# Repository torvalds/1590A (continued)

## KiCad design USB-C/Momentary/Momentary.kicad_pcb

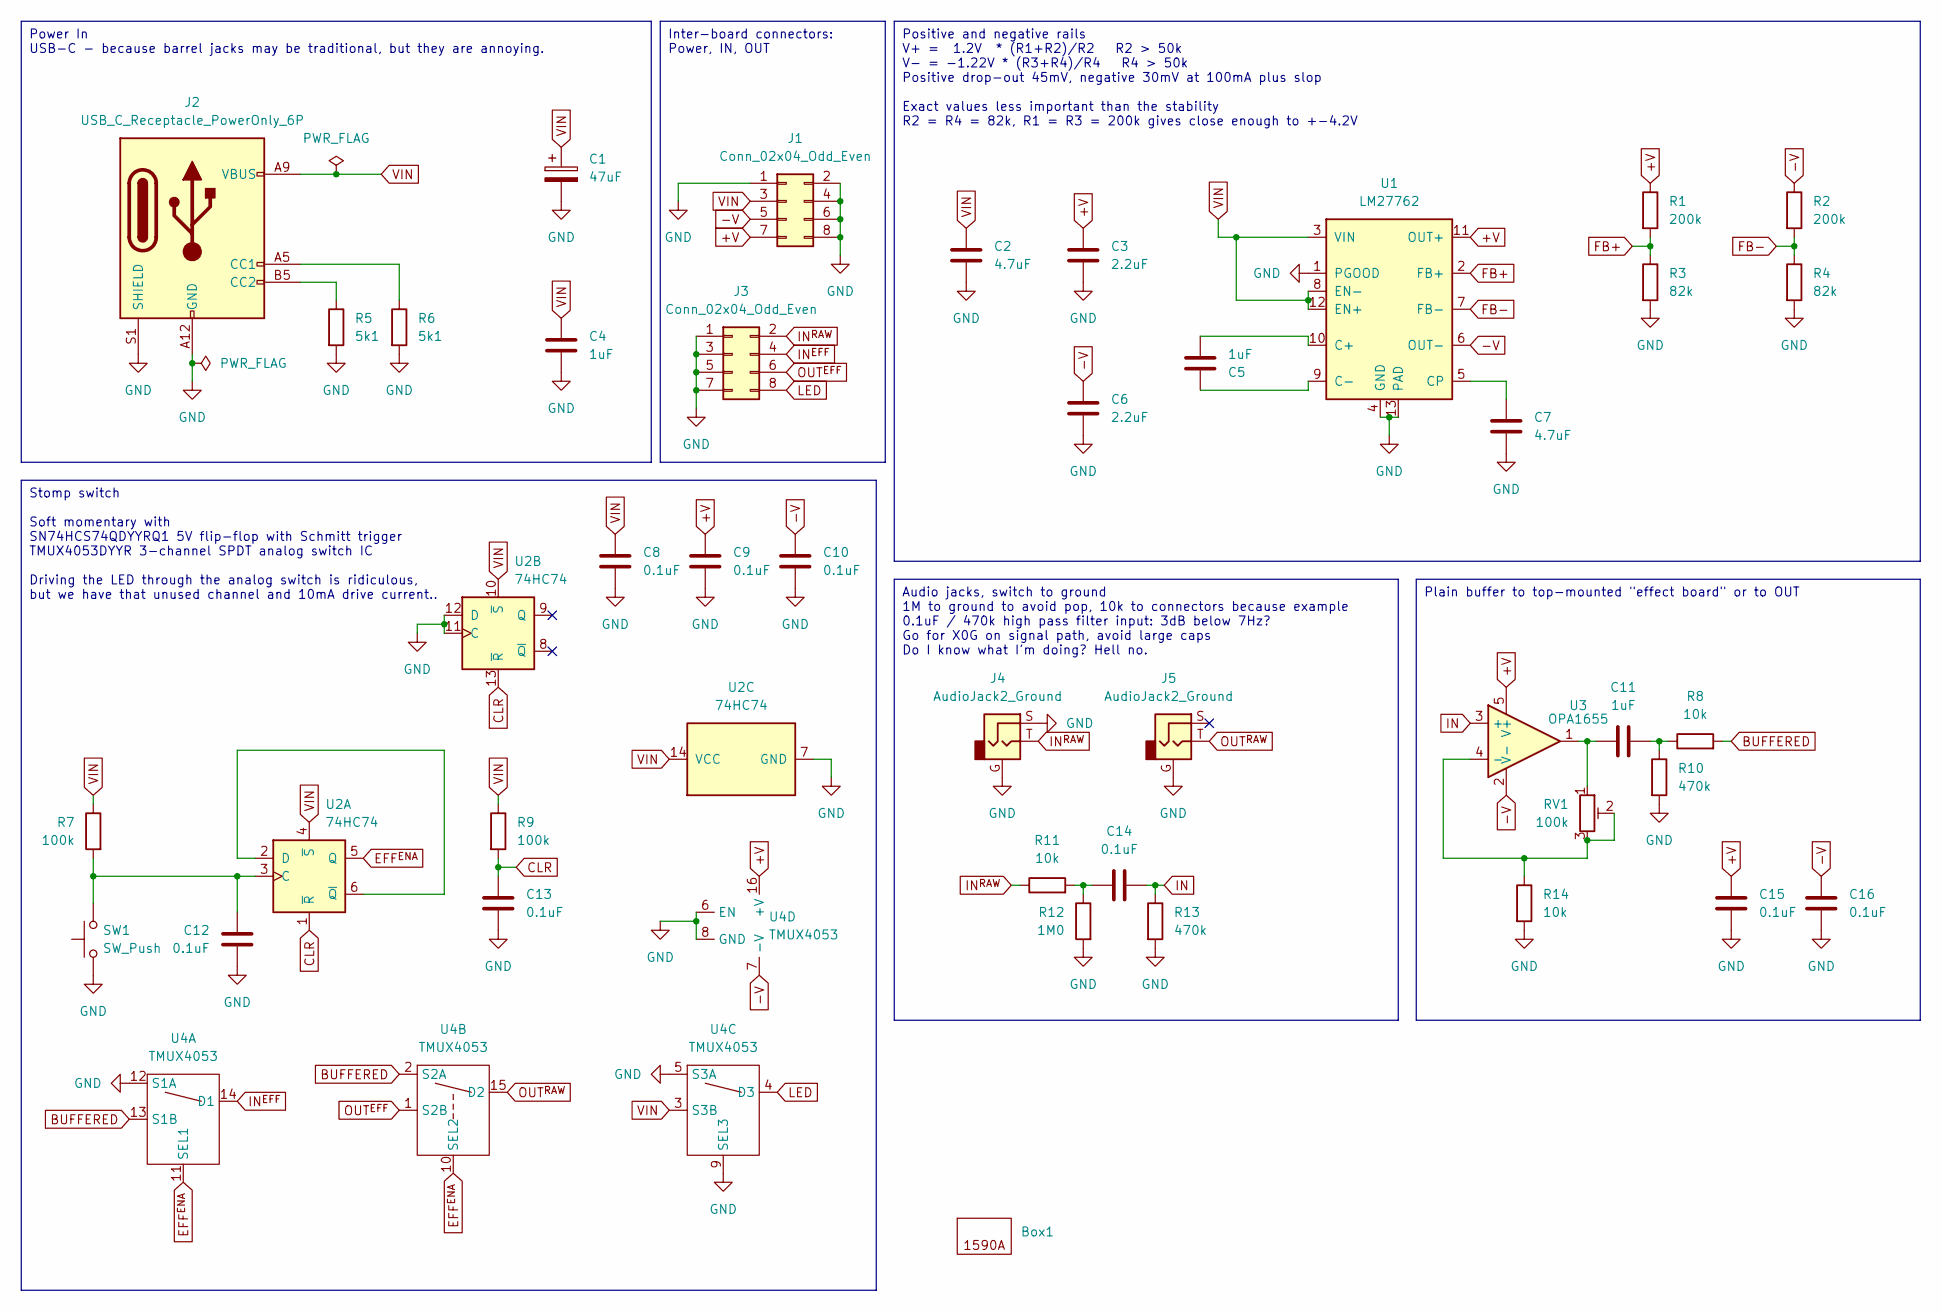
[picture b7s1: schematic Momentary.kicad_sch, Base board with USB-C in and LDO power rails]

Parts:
Box1: 1590A
C1: 47uF; CP_Radial_D5.0mm_P2.00mm
C2, C7: 4.7uF; C_1206_3216Metric_Pad1.33x1.80mm_HandSolder
C3, C6: 2.2uF; C_1206_3216Metric_Pad1.33x1.80mm_HandSolder
C4, C5, C11: 1uF; C_1206_3216Metric_Pad1.33x1.80mm_HandSolder
C8, C9, C10, C12, C13, C14, C15, C16: 0.1uF; C_1206_3216Metric_Pad1.33x1.80mm_HandSolder
J1, J3: Conn_02x04_Odd_Even; PinHeader_2x04_P2.54mm_Vertical
J2: USB_C_Receptacle_PowerOnly_6P; USB_C_Receptacle_GCT_USB4125-xx-x-0190_6P_TopMnt_Horizontal
J4, J5: AudioJack2_Ground; CK-6.35
R1, R2: 200k; R_0805_2012Metric_Pad1.20x1.40mm_HandSolder
R3, R4: 82k; R_0805_2012Metric_Pad1.20x1.40mm_HandSolder
R5, R6: 5k1; R_0805_2012Metric_Pad1.20x1.40mm_HandSolder
R7, R9: 100k; R_0805_2012Metric_Pad1.20x1.40mm_HandSolder
R8, R11, R14: 10k; R_0805_2012Metric_Pad1.20x1.40mm_HandSolder
R10, R13: 470k; R_0805_2012Metric_Pad1.20x1.40mm_HandSolder
R12: 1M0; R_0805_2012Metric_Pad1.20x1.40mm_HandSolder
RV1: 100k; Bourns_3362S
SW1: SW_Push; PinHeader_1x02_P2.54mm_Vertical
U1: LM27762; WSON-12-1EP_3x2mm_P0.5mm_EP1x2.65
U2: 74HC74; SOT-23-THIN-14
U3: OPA1655; SOT-23-5_HandSoldering
U4: TMUX4053; Texas_DYY0016A_TSOT-23-16_4.2x2.0mm_P0.5mm

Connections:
+V: C3.1, C9.1, C15.1, J1.7, R1.1, U1.11 (OUT+), U3.5 (V+), U4.16 (+V)
-V: C6.1, C10.1, C16.1, J1.5, R2.1, U1.6 (OUT-), U3.2 (V-), U4.7 (-V)
BUFFERED: R8.2, U4.2 (S2A), U4.13 (S1B)
CLR: C13.1, R9.2, U2.1 (~R), U2.13 (~R)
EFF^{ENA}: U2.5 (Q), U4.10 (SEL2), U4.11 (SEL1)
FB+: R1.2, R3.1, U1.2 (FB+)
FB-: R2.2, R4.1, U1.7 (FB-)
GND: C1.2, C2.2, C3.2, C4.2, C6.2, C7.2, C8.2, C9.2, C10.2, C12.2, C13.2, C15.2, C16.2, J1.1, J1.2, J1.4, J1.6, J1.8, J2.A12 (GND), J2.B12 (GND), J2.S1 (SHIELD), J3.1, J3.3, J3.5, J3.7, J4.G, J4.S, J5.G, R3.2, R4.2, R5.2, R6.2, R10.2, R12.2, R13.2, R14.2, SW1.1, U1.1 (PGOOD), U1.4 (GND), U1.13 (PAD), U2.7 (GND), U2.11 (C), U2.12 (D), U4.5 (S3A), U4.6 (EN), U4.8 (GND), U4.9 (SEL3), U4.12 (S1A)
IN: C14.2, R13.1, U3.3 (+)
IN^{EFF}: J3.4, U4.14 (D1)
IN^{RAW}: J3.2, J4.T, R11.1
LED: J3.8, U4.4 (D3)
unnamed: C11.1, RV1.1, U3.1
unnamed: C11.2, R8.1, R10.1
unnamed: C14.1, R11.2, R12.1
unnamed: J2.A5 (CC1), R6.1
unnamed: J2.B5 (CC2), R5.1
unnamed: C5.2, U1.10 (C+)
unnamed: C5.1, U1.9 (C-)
unnamed: C7.1, U1.5 (CP)
unnamed: C12.1, R7.2, SW1.2, U2.3 (C)
unnamed: U2.2 (D), U2.6 (~Q)
unnamed: R14.1, RV1.2, RV1.3, U3.4 (-)
OUT^{EFF}: J3.6, U4.1 (S2B)
OUT^{RAW}: J5.T, U4.15 (D2)
VIN: C1.1, C2.1, C4.1, C8.1, J1.3, J2.A9 (VBUS), J2.B9 (VBUS), R7.1, R9.1, U1.3 (VIN), U1.8 (EN-), U1.12 (EN+), U2.4 (~S), U2.10 (~S), U2.14 (VCC), U4.3 (S3B)

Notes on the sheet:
Audio jacks, switch to ground 1M to ground to avoid pop, 10k to connectors because example 0.1uF / 470k high pass filter input: 3dB below 7Hz? Go for X0G on signal path, avoid large caps Do I know what I'm doing? Hell no.
Positive and negative rails V+ = 1.2V * (R1+R2)/R2 R2 > 50k V- = -1.22V * (R3+R4)/R4 R4 > 50k Positive drop-out 45mV, negative 30mV at 100mA plus slop Exact values less important than the stability R2 = R4 = 82k, R1 = R3 = 200k gives close enough to +-4.2V
Plain buffer to top-mounted "effect board" or to OUT
Inter-board connectors: Power, IN, OUT
Power In USB-C - because barrel jacks may be traditional, but they are annoying.
Stomp switch Soft momentary with SN74HCS74QDYYRQ1 5V flip-flop with Schmitt trigger TMUX4053DYYR 3-channel SPDT analog switch IC Driving the LED through the analog switch is ridiculous, but we have that unused channel and 10mA drive current..

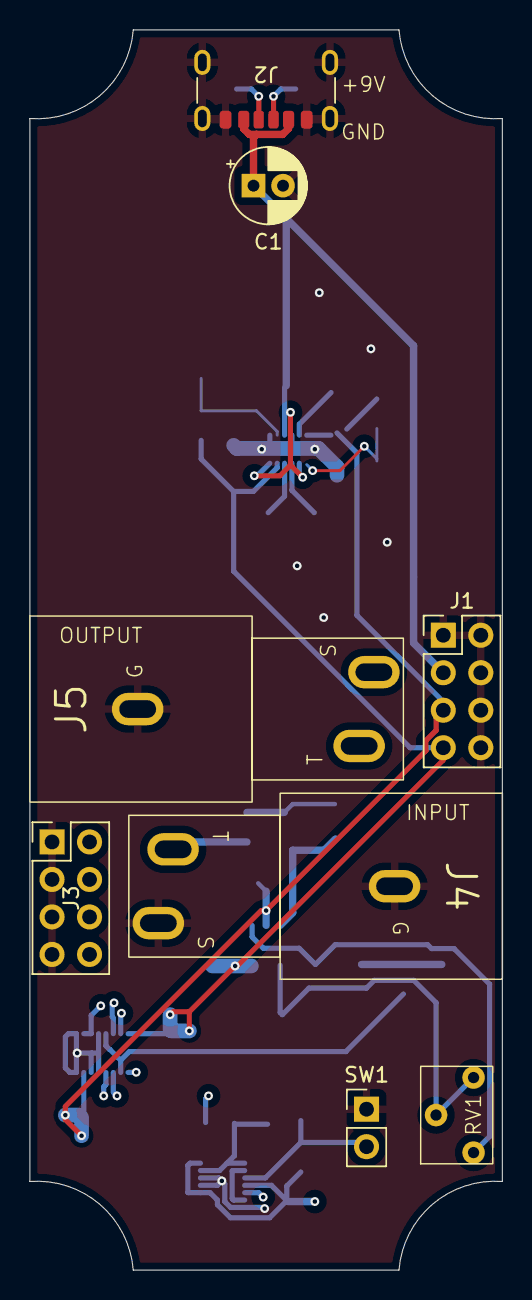
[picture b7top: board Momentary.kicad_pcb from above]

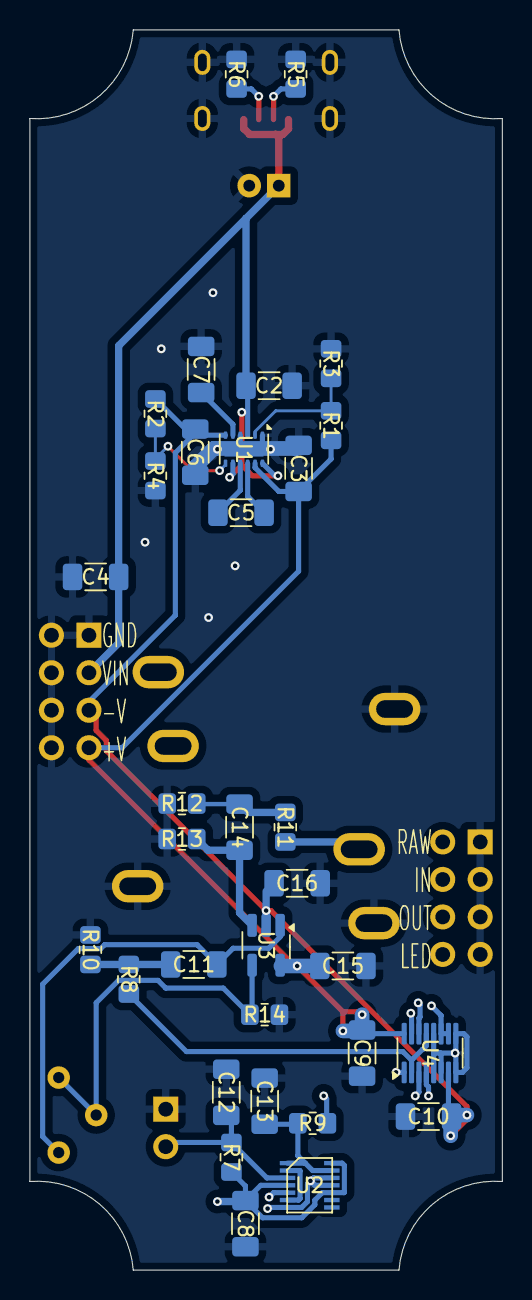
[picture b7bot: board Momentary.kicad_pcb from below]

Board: 4 copper layers, 32.0 x 84.0 mm, 42 parts (33 on the bottom side), 26 nets.
